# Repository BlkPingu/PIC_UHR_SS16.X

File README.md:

# PIC_UHR_SS16.X
digital 2x8 segment clock with additional functions like displaying seconds, adjusting time and potential to add a buzzer

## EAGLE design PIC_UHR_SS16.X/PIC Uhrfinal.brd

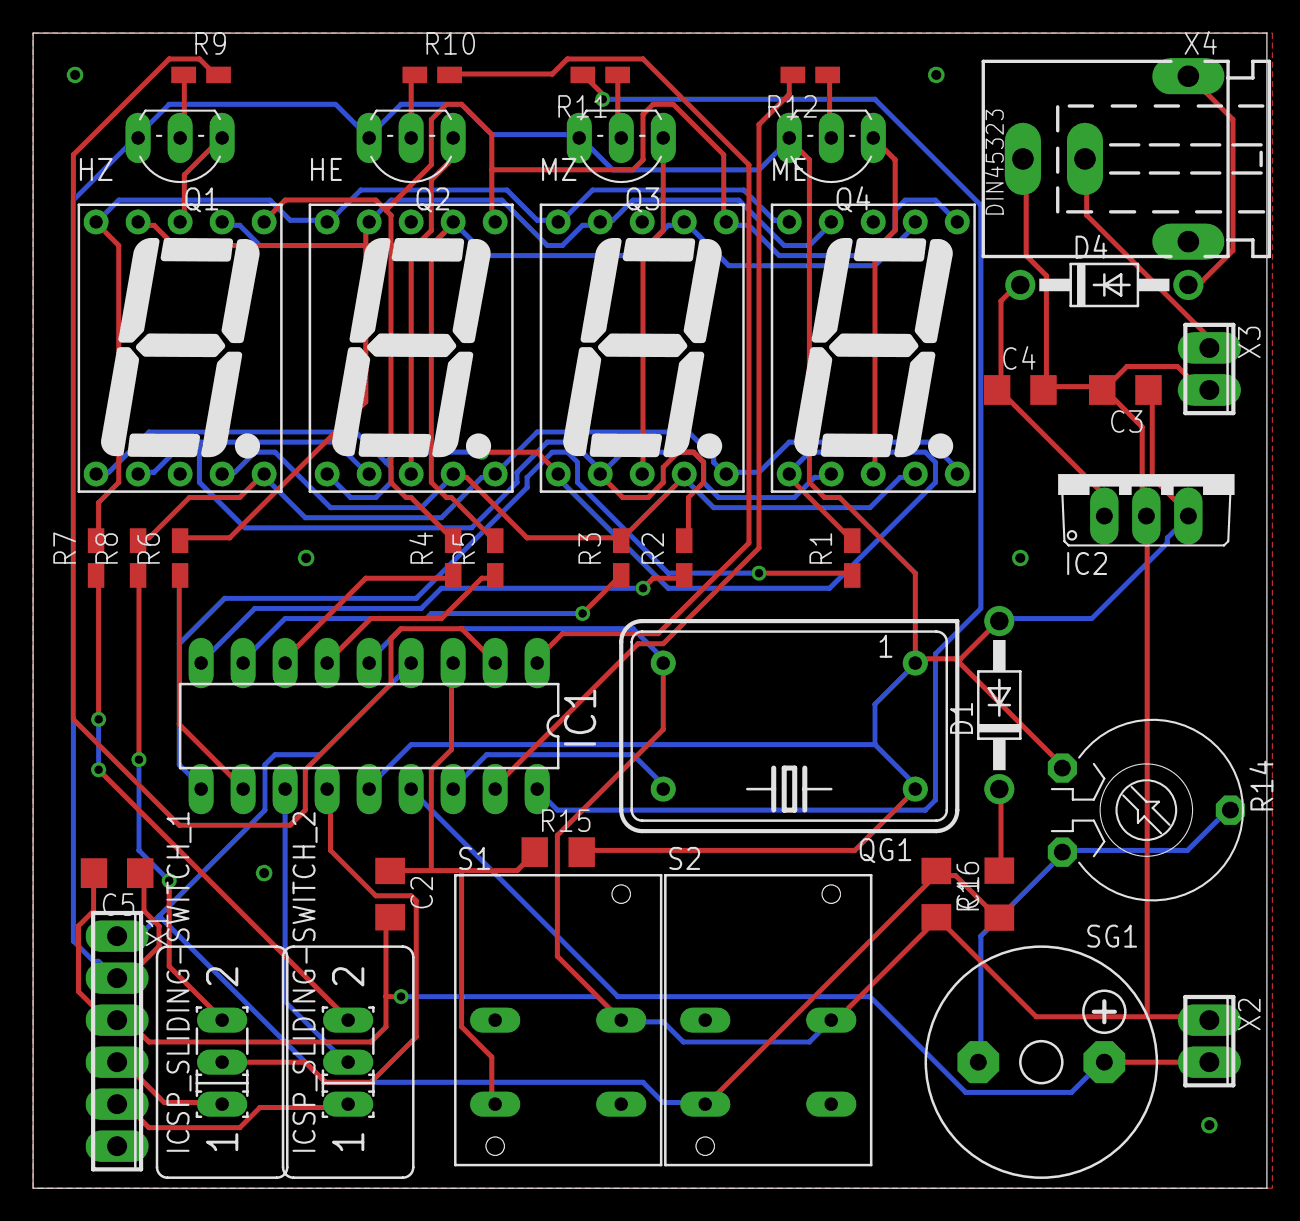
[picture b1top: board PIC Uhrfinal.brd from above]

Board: 2 copper layers, 74.6 x 69.8 mm, 42 parts (0 on the bottom side), 43 nets.

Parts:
C1, C2, C5: 100n; C1206
C3, C4: 0,33µ; C1206
D1, D4: BAT49; DO41-10
HE: 7-SEG_SA52-11; SA52-11
HZ: 7-SEG_SA52-11; SA52-11
IC1: PIC16F1826/27P; DIL18
IC2: 7805TV; TO220V
ICSP_SLIDING-SWITCH_1: _1; M251
ICSP_SLIDING-SWITCH_2: _2; M251
ME: 7-SEG_SA52-11; SA52-11
MZ: 7-SEG_SA52-11; SA52-11
Q1, Q2, Q3, Q4: BC557B; TO92-EBC
QG1: 8 Mhz; DIL14S
R1, R2, R3, R4, R5, R6, R7, R8: 1,5k; R0805W
R9, R10, R11, R12: 2k; R0805W
R14: 25k; PT-10
R15, R16: 10k; R1206
S1, S2: SRK
SG1: F/CM12P
X1: 6POL254
X2: 2POL254
X3: +9V; 2POL254
X4: +9V; 737992-5

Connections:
+5V: C3.1, C5.1, D1.A, IC1.14, IC2.3, Q1.E, Q2.E, Q3.E, Q4.E, QG1.1, QG1.14, R14.1, R15.2, X1.2
BUZZER: IC1.15, SG1.+, X2.2
CLKI: IC1.16, QG1.8
GND: C1.2, C2.2, C3.2, C4.2, C5.2, IC1.5, IC2.2, QG1.7, S1.3, S2.3, X1.3, X2.1, X3.2, X4.+
unnamed: HZ.8, Q1.C
unnamed: Q1.B, R9.1
unnamed: Q2.B, R10.1
unnamed: Q3.B, R11.1
unnamed: HE.3, Q2.C
unnamed: MZ.3, Q3.C
unnamed: ME.3, Q4.C
unnamed: IC1.2, R9.2
unnamed: IC1.1, R10.2
unnamed: HE.10, HZ.10, ME.10, MZ.10, R7.2
unnamed: IC1.18, R11.2
unnamed: IC1.17, R12.2
unnamed: Q4.B, R12.1
unnamed: HE.5, HZ.5, ME.5, MZ.5, R8.2
unnamed: HE.9, HZ.9, ME.9, MZ.9, R6.2
unnamed: HE.7, HZ.7, ME.7, MZ.7, R5.2
unnamed: C4.1, D4.C, IC2.1
unnamed: D4.A, X4.-1
unnamed: HE.1, HZ.1, ME.1, MZ.1, R1.2
unnamed: IC1.11, R6.1
unnamed: IC1.10, R1.1
unnamed: IC1.9, R2.1
unnamed: HE.2, HZ.2, ME.2, MZ.2, R2.2
unnamed: HE.4, HZ.4, ME.4, MZ.4, R3.2
unnamed: IC1.8, R3.1
unnamed: IC1.7, R4.1
unnamed: IC1.6, R5.1
unnamed: ICSP_SLIDING-SWITCH_2.3, R7.1
unnamed: IC1.13, ICSP_SLIDING-SWITCH_1.2
unnamed: IC1.12, ICSP_SLIDING-SWITCH_2.2
unnamed: ICSP_SLIDING-SWITCH_1.3, R8.1
unnamed: ICSP_SLIDING-SWITCH_1.1, X1.4
unnamed: ICSP_SLIDING-SWITCH_2.1, X1.5
unnamed: R14.2, R14.3, SG1.-
unnamed: X3.1, X4.K
unnamed: D1.C, R16.2
unnamed: HE.6, HZ.6, ME.6, MZ.6, R4.2
RA4: C2.1, IC1.3, R15.1, S1.1
RA5: C1.1, IC1.4, R16.1, S2.1, X1.1

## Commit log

2017-10-27 added project
2017-10-31 added brd and sch files for the board
    there seems to be a backward consistency issue with the .brd to .sch, but I recommend rewiring the .sch anyway. You might get better results than me.
